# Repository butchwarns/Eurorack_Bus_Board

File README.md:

# Eurorack_Bus_Board

A simple but versatile bus board for modular synthesizers in the Eurorack format.  
It's cheap and easy to build and has many slots for connecting modules with both 10-pin and 16-pin connectors.

*Eurorack_Bus_Board (v0.1.0)*

## Motivation

I designed this bus board for use in my own modular synthesizer projects. Thought i'd share the board with other synth builders.
(Gerber files in the repo can be directly uploaded to your pcb manufacturer of choice. Interactive BOM for easy assembly included.)

## A word of caution

**CAUTION:** Use the files in this repository at your own risk!  

If you build this bus board (or anything else involved in powering your modules for that matter), be sure you know how to check for errors in the build before actually hooking it up to power or any precious modules! Don't fry a module with a connector wrongly soldered upside down!  

I will do my best to test everything, but the occasional bug might still find its way into the project files. Don't hesitate to report found bugs or share ideas on how to improve the board.

## Project status

The *main* branch of this repository holds the current tested version of the board. All potentially breaking changes will be done on the *develop* branch and the build will be tested before merging. Images in this README do not necessarily show the most recent version of the board, though all images will have version numbers in their title.  

## Tech/framework used

- KiCad

## Features

- Connection for 20 modules (split evenly between 10-pin and 16-pin headers)
- +12V, -12V, +5V
- Follows the Doepfer Eurorack standard including the internal busses for CV and gate.  
- Three LEDs indicate the rails being powered.
- 1.5A max current per rail (can probably take a bit more with appropriate wiring, but better be on the safe side)

Designed to work with the [Eurorack_PSU](https://github.com/butchwarns/Eurorack_PSU/), but can also be used in conjunction with other power supply units.

## Installation

M3 screws and PCB spacers can be used to mount the board to the back of a case.  
Regular 6.3mm flat connectors are used for connecting to the power suppply.

## How to use?

Connect some modules and power the case?  

You can connect power to either side of the board or even chain multiple bus boards in series. (Do not exceed maximum current!)

## How to build?

Upload the *.zip* in the `gerber_files/` folder to your PCB manufacturer's website to order.

An interactive HTML BOM is available in the `bom/` folder. Just open it in a browser and tick off sourced/placed components.  
Also shows where on the board components should be placed.  

**HINT:** Use good quality solder/flux and clean the board thoroughly after soldering!  
Flux residue (especially from low quality solder) may form slightly conductive bridges between power rails, which are very noticeable when there's 40 of them in parallel. I recommend isopropyl alcohol (isopropanol) for cleaning circuit boards.

## Component availability/choices

No unobtainium in this project. All components should be easily sourced.  

Any 1.8mm LEDs will do fine. You might need to tweak the current limiting resistors for equal brightness, which can easily be done on a breadboard.  

Capacitor values are absolutely uncritical as well. The board would probably work with all R,C and LED omitted, although this was neither intended nor tested.

## Contact

Any questions?   

🡢 contact[at]butchwarns.de

## License

*(TODO: Find appropriate open-hardware license!)*

> Until otherwise stated here, the project is default licensed as proprietary.

Build as many of these boards as you want for personal use, but please make it obvious if your build has modified the project files in any way to avoid confusion!  

My name and any logo of mine that might be present on the board design are copyrighted and are not free to use.

Feel free to share the images in the `pictures/` folder of this repository with correct attribution or a link to the project.  

Copr. 2021, Butch Warns

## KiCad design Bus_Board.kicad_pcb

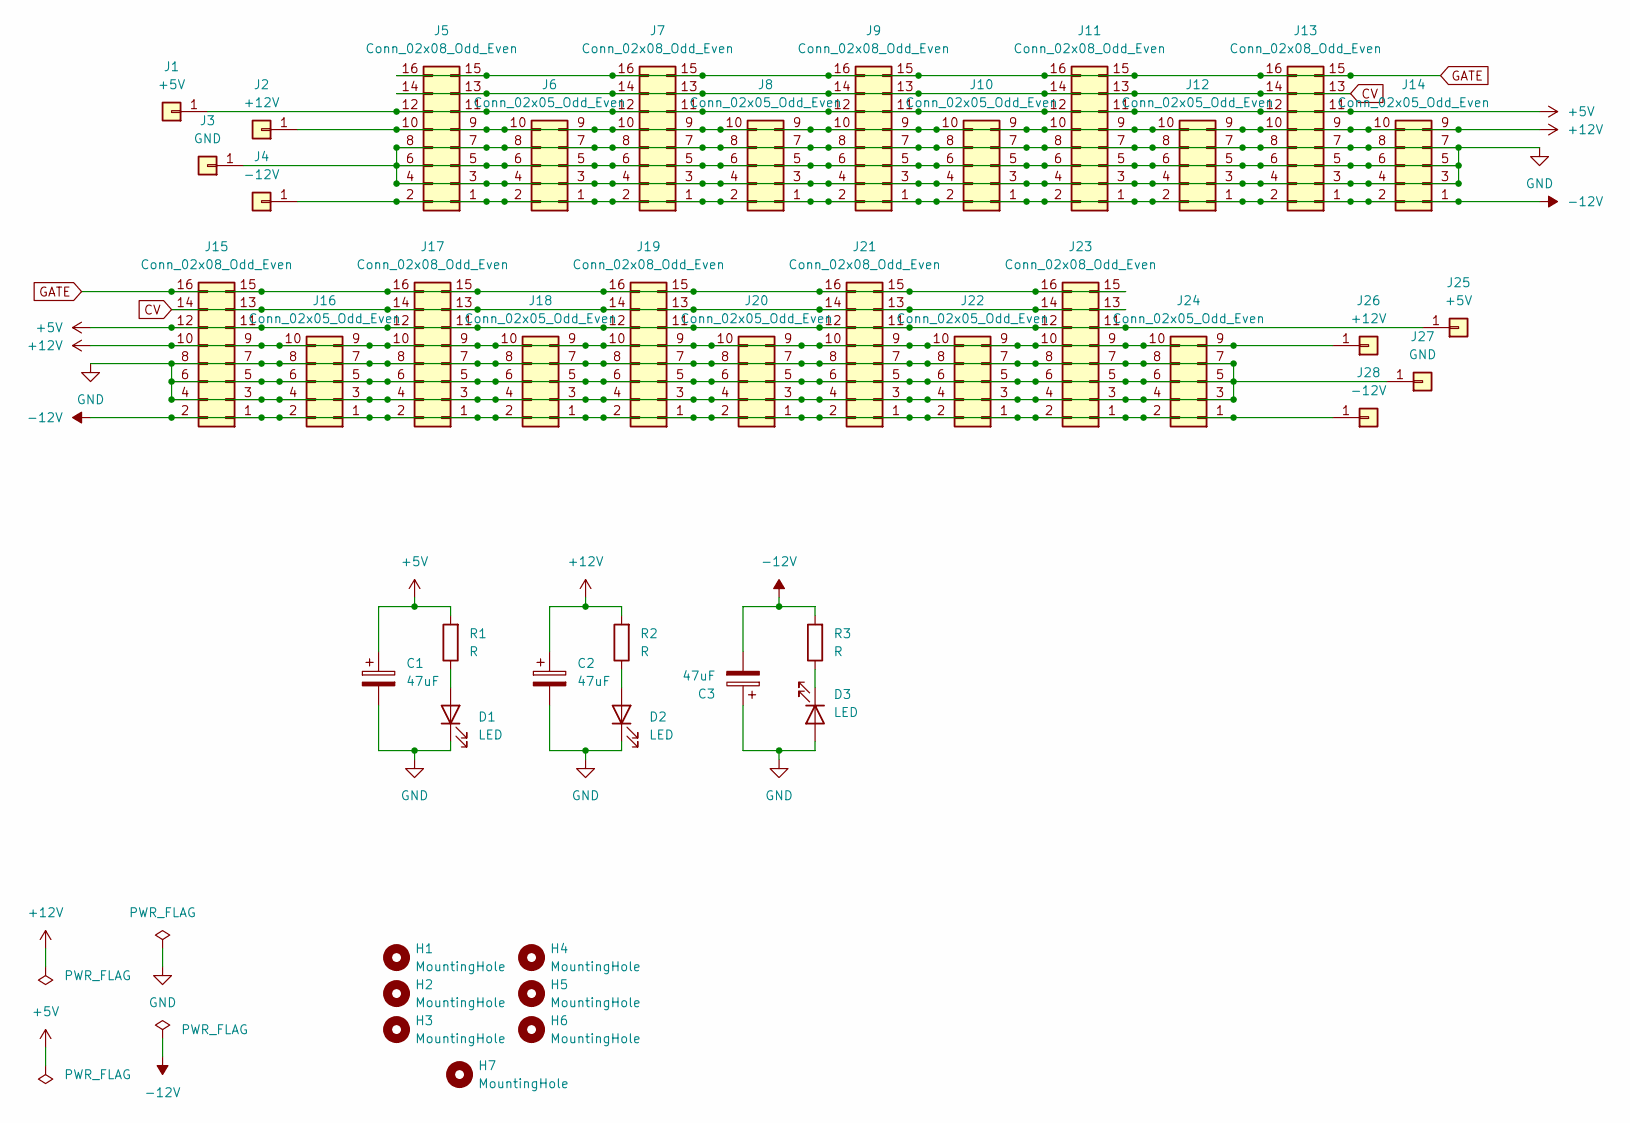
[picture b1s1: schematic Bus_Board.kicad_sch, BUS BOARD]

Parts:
C1, C2, C3: 47uF; CP_Radial_D8.0mm_P3.50mm
D1, D2, D3: LED; LED_D3.0mm
H1, H2, H3, H4, H5, H6, H7: MountingHole; MountingHole_3.2mm_M3
J1, J25: +5V; Flat_Connector_Vogt_6.35mm_P5mm
J2, J26: +12V; Flat_Connector_Vogt_6.35mm_P5mm
J3, J27: GND; Flat_Connector_Vogt_6.35mm_P5mm
J4, J28: -12V; Flat_Connector_Vogt_6.35mm_P5mm
J5, J7, J9, J11, J13, J15, J17, J19, J21, J23: Conn_02x08_Odd_Even; IDC-Header_2x08_P2.54mm_Vertical
J6, J8, J10, J12, J14, J16, J18, J20, J22, J24: Conn_02x05_Odd_Even; IDC-Header_2x05_P2.54mm_Vertical
R1, R2, R3: R; R_Axial_DIN0207_L6.3mm_D2.5mm_P7.62mm_Horizontal

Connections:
+5V: C1.1, J1.1, J5.11, J5.12, J7.11, J7.12, J9.11, J9.12, J11.11, J11.12, J13.11, J13.12, J15.11, J15.12, J17.11, J17.12, J19.11, J19.12, J21.11, J21.12, J23.11, J23.12, J25.1, R1.2
+12V: C2.1, J2.1, J5.9, J5.10, J6.9, J6.10, J7.9, J7.10, J8.9, J8.10, J9.9, J9.10, J10.9, J10.10, J11.9, J11.10, J12.9, J12.10, J13.9, J13.10, J14.9, J14.10, J15.9, J15.10, J16.9, J16.10, J17.9, J17.10, J18.9, J18.10, J19.9, J19.10, J20.9, J20.10, J21.9, J21.10, J22.9, J22.10, J23.9, J23.10, J24.9, J24.10, J26.1, R2.2
-12V: C3.2, J4.1, J5.1, J5.2, J6.1, J6.2, J7.1, J7.2, J8.1, J8.2, J9.1, J9.2, J10.1, J10.2, J11.1, J11.2, J12.1, J12.2, J13.1, J13.2, J14.1, J14.2, J15.1, J15.2, J16.1, J16.2, J17.1, J17.2, J18.1, J18.2, J19.1, J19.2, J20.1, J20.2, J21.1, J21.2, J22.1, J22.2, J23.1, J23.2, J24.1, J24.2, J28.1, R3.2
CV: J5.13, J5.14, J7.13, J7.14, J9.13, J9.14, J11.13, J11.14, J13.13, J13.14, J15.13, J15.14, J17.13, J17.14, J19.13, J19.14, J21.13, J21.14, J23.13, J23.14
GATE: J5.15, J5.16, J7.15, J7.16, J9.15, J9.16, J11.15, J11.16, J13.15, J13.16, J15.15, J15.16, J17.15, J17.16, J19.15, J19.16, J21.15, J21.16, J23.15, J23.16
GND: C1.2, C2.2, C3.1, D1.1 (K), D2.1 (K), D3.2 (A), J3.1, J5.3, J5.4, J5.5, J5.6, J5.7, J5.8, J6.3, J6.4, J6.5, J6.6, J6.7, J6.8, J7.3, J7.4, J7.5, J7.6, J7.7, J7.8, J8.3, J8.4, J8.5, J8.6, J8.7, J8.8, J9.3, J9.4, J9.5, J9.6, J9.7, J9.8, J10.3, J10.4, J10.5, J10.6, J10.7, J10.8, J11.3, J11.4, J11.5, J11.6, J11.7, J11.8, J12.3, J12.4, J12.5, J12.6, J12.7, J12.8, J13.3, J13.4, J13.5, J13.6, J13.7, J13.8, J14.3, J14.4, J14.5, J14.6, J14.7, J14.8, J15.3, J15.4, J15.5, J15.6, J15.7, J15.8, J16.3, J16.4, J16.5, J16.6, J16.7, J16.8, J17.3, J17.4, J17.5, J17.6, J17.7, J17.8, J18.3, J18.4, J18.5, J18.6, J18.7, J18.8, J19.3, J19.4, J19.5, J19.6, J19.7, J19.8, J20.3, J20.4, J20.5, J20.6, J20.7, J20.8, J21.3, J21.4, J21.5, J21.6, J21.7, J21.8, J22.3, J22.4, J22.5, J22.6, J22.7, J22.8, J23.3, J23.4, J23.5, J23.6, J23.7, J23.8, J24.3, J24.4, J24.5, J24.6, J24.7, J24.8, J27.1
unnamed: D1.2 (A), R1.1
unnamed: D2.2 (A), R2.1
unnamed: D3.1 (K), R3.1

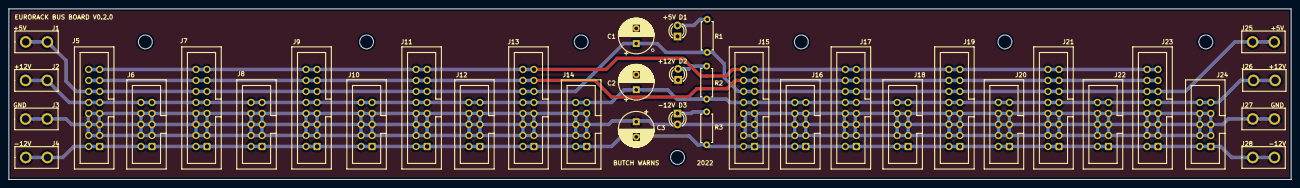
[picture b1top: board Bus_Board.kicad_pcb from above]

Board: 2 copper layers, 295.9 x 39.4 mm, 44 parts (0 on the bottom side), 9 nets.

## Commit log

2022-01-28 Bus Board work in progress.
2022-05-15 Fix orientation of connectors and some other parts
2022-05-15 Fix Bug, add thermal reliefs to groundplane
    Bugfix: reverse polarity of C3 and D3
    Add thermal reliefs in ground plane for easier soldering
2022-05-15 Minor changes
2022-05-15 Connect CV and GATE lines, add ljcpcb order number
2022-06-03 Add photos of an assembled unit and the bare pcb (both v0.1.0)
2022-06-03 Update README.md
    Start writing actual README
2022-06-04 Update README.md
    Continue writing README
2022-06-04 Change text on PCB
2022-06-04 Add interactive HTML BOM
2022-06-04 Add v0.2.0 Gerber files
2022-06-04 Update README.md
    Change wording in README
2022-06-05 Update README.md
    Add max current rating and reword some sentences
2022-06-05 Add values to LEDs and resistors
2022-06-05 Update README.md
    Add reference to Eurorack_PSU in README.md
2022-06-10 Add schematic pdf
2022-06-29 Update README.md
    Add badges
2022-06-30 Update README.md
    Remove unneccessary badge
